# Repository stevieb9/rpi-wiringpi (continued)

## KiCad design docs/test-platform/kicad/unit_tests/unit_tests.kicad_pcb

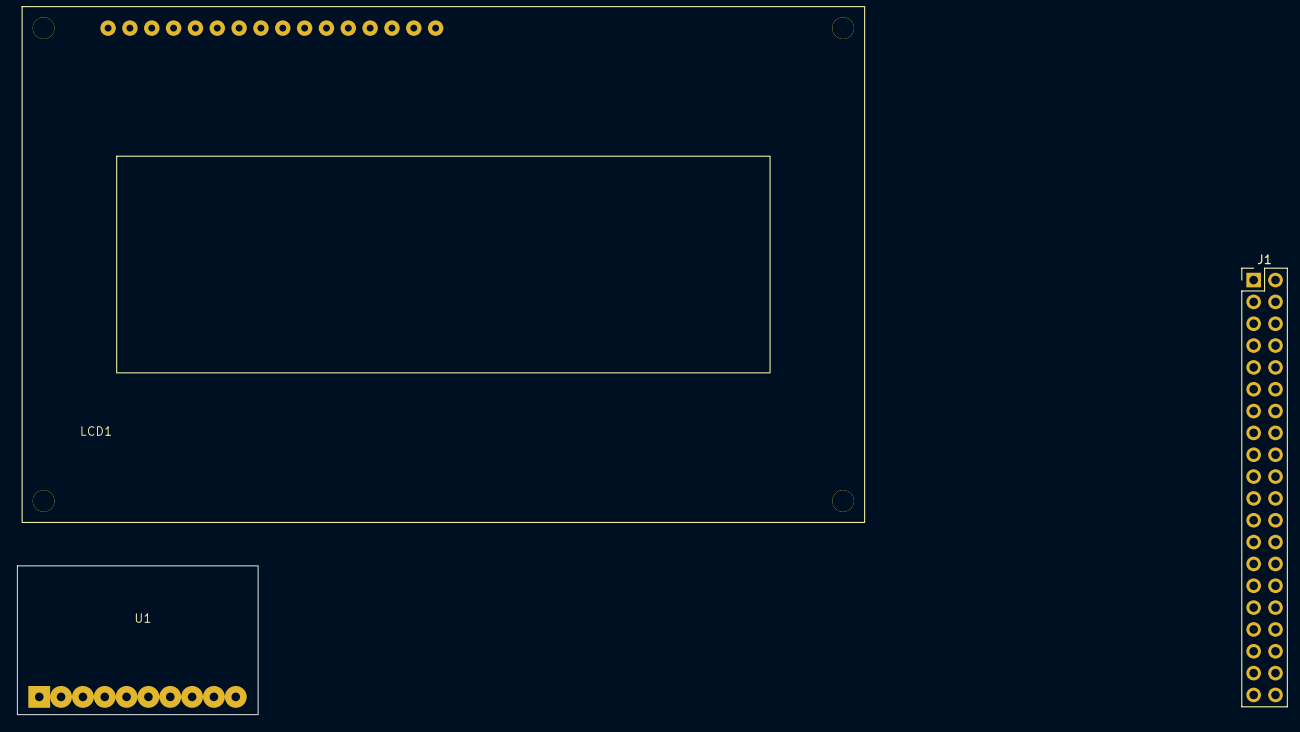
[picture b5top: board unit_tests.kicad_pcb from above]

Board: 2 copper layers, 3 parts (0 on the bottom side), 3 nets, no tracks yet.

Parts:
J1: Raspberry_Pi_4; PinHeader_2x20_P2.54mm_Vertical
LCD1: LCD_HD44780; HD44780_LCD_Module
U1: ADS1115; ADS1115_Breakout

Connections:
unnamed: J1.1 (3V3), J1.17 (3V3)
unnamed: J1.2 (5V), J1.4 (5V)
unnamed: J1.6 (GND), J1.9 (GND), J1.14 (GND), J1.20 (GND), J1.25 (GND), J1.30 (GND), J1.34 (GND), J1.39 (GND)

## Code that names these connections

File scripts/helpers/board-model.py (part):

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   '14':'VOUTA','13':'VREFA','12':'AVSS','11':'VREFB','10':'VOUTB'}),
 'U5': ('MCP42010', 'DIP-14', {  # dual SPI digital pot (ch0 used)
   # Pinout per Microchip DS11195C (corrected: pins 8-14 were reverse-numbered).
   '1':'CS','2':'SCK','3':'SI','4':'VSS','5':'PB1','6':'PW1','7':'PA1',
   '8':'PA0','9':'PW0','10':'PB0','11':'RS','12':'SHDN','13':'SO','14':'VDD'}),
 # --- sensor / breakout modules ---
 'M1': ('ADS1015_0x48', 'Module', {'VDD':'VDD','GND':'GND','SCL':'SCL','SDA':'SDA','ADDR':'ADDR','ALRT':'ALRT','A0':'A0','A1':'A1','A2':'A2','A3':'A3'}),  # ALRT = ALERT/RDY (TI SBAS444E pin 2), on the module header between ADDR and A0; unused
 'M3': ('DS3231_ZS042', 'Module', {'VCC':'VCC','GND':'GND','SCL':'SCL','SDA':'SDA','SQW':'SQW','32K':'32K'}),  # +AT24C32 onboard
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 'SV1': ('Servo', 'Conn-3', {'SIG':'SIG','V+':'V+','GND':'GND'}),
 # --- passives ---
 'RV1': ('10k_pot', 'Pot', {'1':'A','2':'W','3':'B'}),     # LCD contrast
 'SW1': ('CW_limit_switch', 'SW', {'1':'1','2':'2'}),   # magnetic, GPIO17 <-> +3V3
 'SW2': ('CCW_limit_switch', 'SW', {'1':'1','2':'2'}),  # magnetic, GPIO27 <-> +3V3
 'D1': ('centre_LED', 'LED', {'A':'A','K':'K'}),        # GPIO19 via R8
 'R8': ('330', 'R', {'1':'1','2':'2'}),                 # centre-LED series
 'R7': ('220', 'R', {'1':'1','2':'2'}),  # LCD backlight series
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 ('SPI_MOSI',[('J1','19'),('U3','11'),('U4','5'),('U5','3')]),
 ('SPI_MISO',[('J1','21'),('U3','12')]),
 ('SPI_SCLK',[('J1','23'),('U3','13'),('U4','4'),('U5','2')]),
 ('CS_ADC', [('J1','37'),('U3','10')]),   # GPIO26
 ('CS_DAC', [('J1','32'),('U4','3')]),    # GPIO12
 ('CS_DPOT',[('J1','33'),('U5','1')]),    # GPIO13
 # shift register
 ('SR_DATA', [('J1','40'),('U2','14')]),  # GPIO21
 ('SR_CLK',  [('J1','38'),('U2','11')]),  # GPIO20
 ('SR_LATCH',[('J1','36'),('U2','12')]),  # GPIO16
 # LCD (HD44780, 4-bit)
 ('LCD_RS',[('J1','29'),('M8','4')]),     # GPIO5
 ('LCD_E', [('J1','31'),('M8','6')]),     # GPIO6
 ('LCD_D4',[('J1','7'), ('M8','11')]),    # GPIO4
 ('LCD_D5',[('J1','11'),('M8','12'),('SW1','1')]),    # GPIO17 (+ stepper CW limit switch)
 ('LCD_D6',[('J1','13'),('M8','13'),('SW2','1')]),    # GPIO27 (+ stepper CCW limit switch)
 ('LCD_D7',[('J1','15'),('M8','14')]),    # GPIO22
 ('LCD_V0',[('M8','3'),('RV1','2')]),     # contrast wiper
 ('LCD_BL',[('M8','15'),('R7','2')]),     # backlight anode via R7
 # PWM18 -> ADS#1 A0 and servo
 ('PWM18',[('J1','12'),('M1','A0'),('SV1','SIG')]),  # GPIO18
 # UART loopback
 ('UART_LOOP',[('J1','8'),('J1','10')]),  # GPIO14 TXD <-> GPIO15 RXD
 # analog loop-backs
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]

# Pi 40-pin header native functions (orientation only; standard Pi pinout).
J1FUNC = {1:'3V3',2:'5V',3:'GPIO2/SDA',4:'5V',5:'GPIO3/SCL',6:'GND',7:'GPIO4',8:'GPIO14/TXD',
 9:'GND',10:'GPIO15/RXD',11:'GPIO17',12:'GPIO18',13:'GPIO27',14:'GND',15:'GPIO22',16:'GPIO23',
 17:'3V3',18:'GPIO24',19:'GPIO10/MOSI',20:'GND',21:'GPIO9/MISO',22:'GPIO25',23:'GPIO11/SCLK',
 24:'GPIO8',25:'GND',26:'GPIO7',27:'GPIO0',28:'GPIO1',29:'GPIO5',30:'GND',31:'GPIO6',32:'GPIO12',
 33:'GPIO13',34:'GND',35:'GPIO19',36:'GPIO16',37:'GPIO26',38:'GPIO20',39:'GND',40:'GPIO21'}

# which node(s) drive each net (become 'output'); 'REF' = all pins of REF, 'REF*PIN' = just that pin
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
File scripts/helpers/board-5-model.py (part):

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  LCD1  HD44780 20x4 character LCD, 4-bit bus -- t/525. 5V powered, but driven
        with 3V3 logic straight from the Pi GPIO (HD44780 reads VIH ~= 0.7*VDD,
        and 3V3 clears that at VDD=5V on these panels; no shifter on the LCD bus).
          RS=GPIO5  E=GPIO6  D4=GPIO4  D5=GPIO17  D6=GPIO27  D7=GPIO22
        D0-D3 (pins 7-10) are unused in 4-bit mode; RW (pin 5) is tied low
        (write-only). Contrast (V0) from an on-board trimpot; backlight A straight
        to +5V (the LCD module carries its own series resistor, R8), K to GND.
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  J2  signal in  (JST-4): 1:SDA 2:SCL 3:TX14 4:RX15   (I2C bus + the UART pair)
  J3  LCD GPIO in(JST-6): 1:RS 2:E 3:D4 4:D5 5:D6 6:D7 (the six Pi GPIO that drive
                          the LCD; silk shows the LCD role, the net is the BCM
                          GPIO it carries -- GPIO17/GPIO27 are SHARED with board 3's
                          stepper limit switches, platform doc section 10-10)
  J4  I2C out    (JST-4): 1:SDA 2:SCL 3:+5V 4:GND     (5V I2C out to the external
                          Arduino; common GND is mandatory for the bus, +5V is an
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 ('SDA_5V',[('U1','HV1'),('J4','1')]),
 ('SCL_5V',[('U1','HV2'),('J4','2')]),
 # UART loop-back: Pi TXD14 / RXD15 arrive on J2, bridged by the JP1 shunt
 ('UART_TX',[('J2','3'),('JP1','1')]),   # GPIO14 (TXD)
 ('UART_RX',[('J2','4'),('JP1','2')]),   # GPIO15 (RXD)
 # LCD control + 4-bit data (Pi GPIO in on J3). Net = BCM GPIO; GPIO17/GPIO27 are
 # SHARED with board 3's stepper limit switches (platform doc section 10-10).
 ('GPIO5', [('J3','1'),('LCD1','4')]),    # RS
 ('GPIO6', [('J3','2'),('LCD1','6')]),    # E (strobe)
 ('GPIO4', [('J3','3'),('LCD1','11')]),   # D4
 ('GPIO17',[('J3','4'),('LCD1','12')]),   # D5
 ('GPIO27',[('J3','5'),('LCD1','13')]),   # D6
 ('GPIO22',[('J3','6'),('LCD1','14')]),   # D7
 # LCD local analog: contrast wiper -> V0, backlight resistor -> A
 ('LCD_V0',[('RV1','2'),('LCD1','3')]),
]
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 'I2C_SDA':'J2', 'I2C_SCL':'J2',
 'SDA_5V':'U1', 'SCL_5V':'U1',          # the shifter drives the 5V side
 'UART_TX':'J2', 'UART_RX':'JP1',       # RX is fed by the loop-back jumper
 'GPIO5':'J3', 'GPIO6':'J3', 'GPIO4':'J3',
 'GPIO17':'J3', 'GPIO27':'J3', 'GPIO22':'J3',
 'LCD_V0':'RV1',
}

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# per-subsystem sheets (cleaner reads)
SHEETS = {
 'i2c':  {'I2C_SDA','I2C_SCL','SDA_5V','SCL_5V'},
 'lcd':  {'GPIO5','GPIO6','GPIO4','GPIO17','GPIO27','GPIO22','LCD_V0'},
 'uart': {'UART_TX','UART_RX'},
}

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
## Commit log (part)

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2026-06-05 Bump prereq of WiringPi::API to 3.1801
2026-06-05 Added new refactoring plan
2026-06-05 Move past plans to plans/
2026-06-06 fix logic bug
2026-06-06 Fix _pin_registration ownership guard and meta references
    Core.pm:275 negation precedence (! ... eq) left the unregister
    ownership guard dead; use ne. Switch :299/:310 from ->{meta}
    to the local and add the missing ; at :307.
2026-06-06 Add interrupt_dropped proxy and document it
    Wrap WiringPi::API::interrupt_dropped() as a method so the whole
    interrupt-control surface is proxied consistently. Add its POD and
    update INTERRUPTS.md to call ->interrupt_dropped.
2026-06-06 Clarify interrupt/pin POD and flag background_interrupt dependency
2026-06-06 Bump VERSION to 3.1800 and record Core/POD fixes in Changes
2026-06-06 Split test pin-config into per-board tables (pi3/pi4/pi5)
2026-06-06 Added temporary UNWRAPPED
2026-06-06 drwxrwxr-x 2 steve steve 4096 Jun 4 14:18 patch
2026-06-06 Strengthen checksum() UUID entropy with PID + hi-res time
2026-06-06 Remove setup_phys()/setup_sys() init support and PHYS/SYS pin schemes
2026-06-06 Finished setup mode changes
2026-06-06 Move finished plans to plans/done
2026-06-06 Add OO worker() method to RPi::WiringPi
2026-06-06 Add t/213-worker.t for the OO worker() method
2026-06-06 Add OO worker() valgrind exerciser
2026-06-06 Rename storable plan
2026-06-06 Documented threads
2026-06-06 rewrite Meta.pm onto IPC::Shareable
2026-06-06 add no-XS functional gate for the Shareable backend
2026-06-06 update t/02-shm_key.t for crc32-derived meta_key
2026-06-06 Fix unregister_pin ownership guard never deleting the pin
2026-06-06 Update Meta.pm POD for IPC::Shareable backend (CRC32 key, locking)
2026-06-08 Fix global-destruction warnings with END-time object cleanup
2026-06-08 Add tests to ensure meta data takes up only a single segment
2026-06-08 Added meta_remove(); deletes the shared mem segment
2026-06-08 Numerous tweaks; Bump RPi::SysInfo to 1.01 and update sysinfo tests for current Pi OS
    RPi::SysInfo 1.01 fixes gpio_info() (now pinctrl) and raspi_config()
    (now /boot/firmware/config.txt). Update t/403/404/406/407 to the
    corrected output: patterns made board/OS-agnostic with added assertions
    (gpio line counts/format, config.txt directives/comment-stripping, df
    structure, cpuinfo Revision/Serial/Model).
2026-06-08 Rework crash/signal handling: drop __DIE__ trap, make fatal_exit real
2026-06-08 Fix RP1 (Pi 5) pin restore for INPUT/OUTPUT
2026-06-08 Make t/107 board-aware
2026-06-09 Code tidying
2026-06-09 Pi 5 power/IO leds are wired differently; figure out what board we're on and act accordingly
2026-06-09 Document more unit test env vars
2026-06-09 Correct test issues; using $^X for perl, adding env vars
2026-06-09 Servo tests now auto-cleanup on failure
2026-06-09 ate I2C-bus tests behind RPI_I2C; document test pinout
    Add rpi_i2c_check() and gate t/109, t/140 and t/325 so the I2C-ADC
    tests skip when the bus is disabled instead of dying mid-run and
    leaving stale shared-memory metadata that cascades into later tests.
2026-06-09 RPI_OBJECT_COUNT cleanup
2026-06-09 Moved test-pinout file
2026-06-09 Update tests, add base schematics
2026-06-10 Cleanup in Core
2026-06-10 Clean up Meta pod
2026-06-10 Update ver and copyright
2026-06-10 Build automator scripts to generate markdown pod, and the entire unit test platform documentation
2026-06-10 Add new method to identify Pi board in reference to serial config
2026-06-10 Major POD cleanup; prep for 3.1802 release
2026-06-10 Rework tests and documentation after enabling interfaces on rpi1
2026-06-10 Updated new compliance plan
2026-06-11 Fix release-blocking MANIFEST drift; skip dev-only paths
2026-06-11 Fix 5 HIGH-severity bugs in Core.pm/WiringPi.pm
    gpio_layout() self-recursion; pwm_mode() getter croak; _pwm_in_use()
    &&/|| guard leaking pwm.users meta; cleanup() dropping shared pins for
    all co-owners; falsy RPI_PIN_MODE (WPI=0) restamping scheme to GPIO.
2026-06-11 Fix 5 HIGH-severity bugs; constify PWM default range/mode
    gpio_layout() self-recursion; pwm_mode() getter croak; _pwm_in_use()
    &&/|| guard; cleanup() dropping shared pins for co-owners; falsy
    RPI_PIN_MODE restamp. PWM defaults now use PWM_DEFAULT_RANGE/_MODE.
2026-06-11 Fix HIGH-severity and robustness bugs in Core/Meta/WiringPi
    gpio_layout() recursion, pwm_mode() getter croak, _pwm_in_use guard,
    per-uuid pin cleanup, falsy RPI_PIN_MODE restamp. Add _meta_txn so
    meta locks always release on die; restore signal handlers (incl.
    non-CODE) when the last object cleans up; make fatal_exit per-object;
    check LED sysfs write status; constify PWM defaults.
2026-06-11 Fix HIGH-severity and robustness bugs in Core/Meta/WiringPi
    gpio_layout() recursion, pwm_mode() getter croak, _pwm_in_use guard,
    per-uuid pin cleanup, falsy RPI_PIN_MODE restamp. Add _meta_txn so
    meta locks always release on die; restore signal handlers (incl.
    non-CODE) when the last object cleans up; make fatal_exit per-object;
    check LED sysfs write status; constify PWM defaults. Regression
    coverage in new t/104 + t/154 and extended t/03 + t/153.
2026-06-11 Regenerate README and docs/pod md from current POD
2026-06-11 Fix POD errors across modules; refresh README and generated md
2026-06-11 Fix test-suite correctness: CS pins 12/26 reset-verified again
    RPI_ARDUINO skip-msg typo; t/920 checks the real /dev/shm lock path;
    12/26 restored to pin tables as mode-only checks (level depends on
    attached device); verify reports the offending pin; rpi_i2c_check
    skip msg documents the ADS1115 requirement.
2026-06-11 Harden test suite: CS pin verification, die-safe cleanup, -j1 note
    Restore 12/26 as mode-only checks; report offending pin on verify
    failure; fix RPI_ARDUINO typo and t/920's lock path; END cleanup
    guards in device tests; document the serial-only requirement.
2026-06-11 Fix new() setup param: case-insensitive, croak on unknown, document
    'Gpio'/'GPIO' previously fell through to silent no-init; 'none' is
    now an explicit sentinel branch. Param documented in POD with
    regression tests in t/104. Ignore Python bytecode caches.
2026-06-11 Croak instead of returning undef silently; test hygiene fixes
2026-06-11 Fix bin/pinmap undef warnings; bin/pimetaerase //= cosmetic fixes
2026-06-11 Use numeric == for pin scheme comparison in Util.pm pin_map()
2026-06-11 Document diamond-inheritance MRO in WiringPi.pm/Core.pm
2026-06-11 t/200-209: count interrupt callbacks in a lexical, not {PI_INTERRUPT}
2026-06-11 Drop redundant RPI_POD gate; RPI_RELEASE_TESTING alone enables POD tests
2026-06-11 Single-source PWM/ADC acceptance windows; fix t/109 vacuous bounds
2026-06-11 Replace fixed test settle sleeps with bounded poll-until loops
2026-06-11 gen-schematic.py: write outputs via context managers with error handling
2026-06-11 Renamed test var PI_BOARD to RPI_BOARD
2026-06-11 Generate README.md from POD via gen-pod-md.pl; drop pod2text README
2026-06-11 Allow RPI_DIST_RELEASE=1 to bypass Makefile.PL hardware checks
2026-06-12 Bump versions
2026-06-12 Reorganize unit tests; make dist now rebuilds MD and test-platform files
2026-06-12 Cleanup
2026-06-12 make dist now properly recreates the test-platform data
2026-06-12 3.1802
2026-06-12 Prep for 3.1803
2026-06-12 Updated wiringpi.com links to go to the repo instead
2026-06-13 Refactor interrupt and threads examples
2026-06-13 Generate openable KiCad project for the test platform
2026-06-13 Added Kicad files
2026-06-13 Assign generated footprints and validate KiCad schematic-to-PCB transfer
2026-06-13 Fix U-devices to be proper DIPs
2026-06-13 Test updates temp
2026-06-17 Added power/current info
2026-06-19 Test updates, added tests for new A# B# expander constants
2026-06-19 Begin subifying tests
2026-06-19 Finished subifying tests
2026-06-19 Expander for stepper tests now at 0x21 I2C address
2026-06-19 Refactor unit tests in prep for PCB creation
2026-06-19 Update test docs after unit test changes for expander and stepper
2026-06-19 Removed PDF creation of test docs
2026-06-19 Add protection racket for stepper tests
2026-06-19 Preparation for reorganization of docs/test-platform
2026-06-19 test-platform singularity project updates
2026-06-19 More automation singularity work on test-platform
2026-06-19 Singular point of data for test-platform completed
2026-06-19 Finalization of test-platform automation
2026-06-19 Added KiCAD board 3
2026-06-21 Completely finished unit test board #3 (production ordered)
2026-06-21 Finalize board 3
2026-06-22 Added all data for test board 4
2026-06-22 ...actually added the files
2026-06-22 Added pic of board3
2026-06-22 Updated layouts for boards
2026-06-22 Stabilization of PCB create artifacts
2026-06-22 Add differential arguments of pcb vs code
2026-06-22 Added datasheet audit plan
2026-06-22 Benchmarking dev boards
2026-06-23 Bump ver of RPi::RTC::DS3231
2026-06-23 Added I2C env var for sudo user
2026-06-23 Bump prereq of RPi::ADC::ADS
2026-06-23 pwm/adc updates
2026-06-23 Cleaned up documentation
2026-06-23 Bump prereq of RPi::Const to 1.06
2026-06-23 BMP POD fixes
2026-06-23 Update dpot kicad files to enable pot 2
2026-06-23 Combined and merged Jx connectors
2026-06-23 Renumbered Jx connectors after consolotiation
2026-06-23 Cleanup traces
2026-06-23 Fixed pin18 reset to default tests
2026-06-23 Added tests for sweeping the second dpot channel
2026-06-23 Add ALRT pin to ADS1115; update all pin/pad labels
2026-06-23 Reshape schematic so all elements snap to grid 50 (1.27mm)
2026-06-23 Added N/C to unconnected pins; Swapped out double pole switch for single
2026-06-23 Added tests for fixed shutdown() in the dpot library
2026-06-23 Add I2C gate in sudo
2026-06-23 Fix MCP3008 CS pin stranded at INPUT
2026-06-23 Fix MCP4922 POD issue
2026-06-23 Added mounting holes
2026-06-23 Auto-set individual testing env vars for RPI_BOARD_2
2026-06-23 Rename test script
2026-06-24 RPI_BOARD_3 will now set env vars for the appropriate tets
2026-06-24 Finalized test board 2; sent for production
2026-06-24 Added test board 3 helper script
2026-06-24 Added test board 5
2026-06-24 Work on test board 5
2026-06-24 Corrected level shifter footprint
2026-06-24 Fixed footprint of level shifter
2026-06-24 Updated footprint for trimpot
2026-06-24 Finished KiCAD test board 5
2026-06-24 Added RPI_BOARD_5 env var gate for unit tests
2026-06-24 Classify as board 2 and board 3 as completed
2026-06-24 Updated test board status
2026-06-24 Test README cleanup, add unit test coverage plan
2026-06-24 Update tests in Const
2026-06-24 Updated plan
2026-06-24 Add Pin croak/die validation tests
2026-06-24 Added additional dpot tests
2026-06-24 Added DAC register tests
2026-06-24 Finalization work on test board 5
2026-06-24 Additional tests for ADS1015
2026-06-24 Add MCP23017 tests
2026-06-24 Added KiCAD board 4
2026-06-24 Added EEPROM validation tests
2026-06-24 Add wiringpi-api tests
2026-06-24 Test modifications, gates
2026-06-24 Updated FAQ with new test file info
2026-06-24 Add tests to cover alt pin restore
2026-06-24 Renumber unit tests to fit in line with the new hardware test platform
2026-06-24 Renaming tests
2026-06-24 Added new i2c unit test file
2026-06-24 Added ability for lcd() to manage the I2C expanded LCD screen
2026-06-24 Test cleanup after mass renumbering
2026-06-24 Added decoupling caps
2026-06-24 FAQ test file table now automatically generated
2026-06-24 Simplified test file table in FAQ
2026-06-24 Update plan to remember to refactor FAQ test section
